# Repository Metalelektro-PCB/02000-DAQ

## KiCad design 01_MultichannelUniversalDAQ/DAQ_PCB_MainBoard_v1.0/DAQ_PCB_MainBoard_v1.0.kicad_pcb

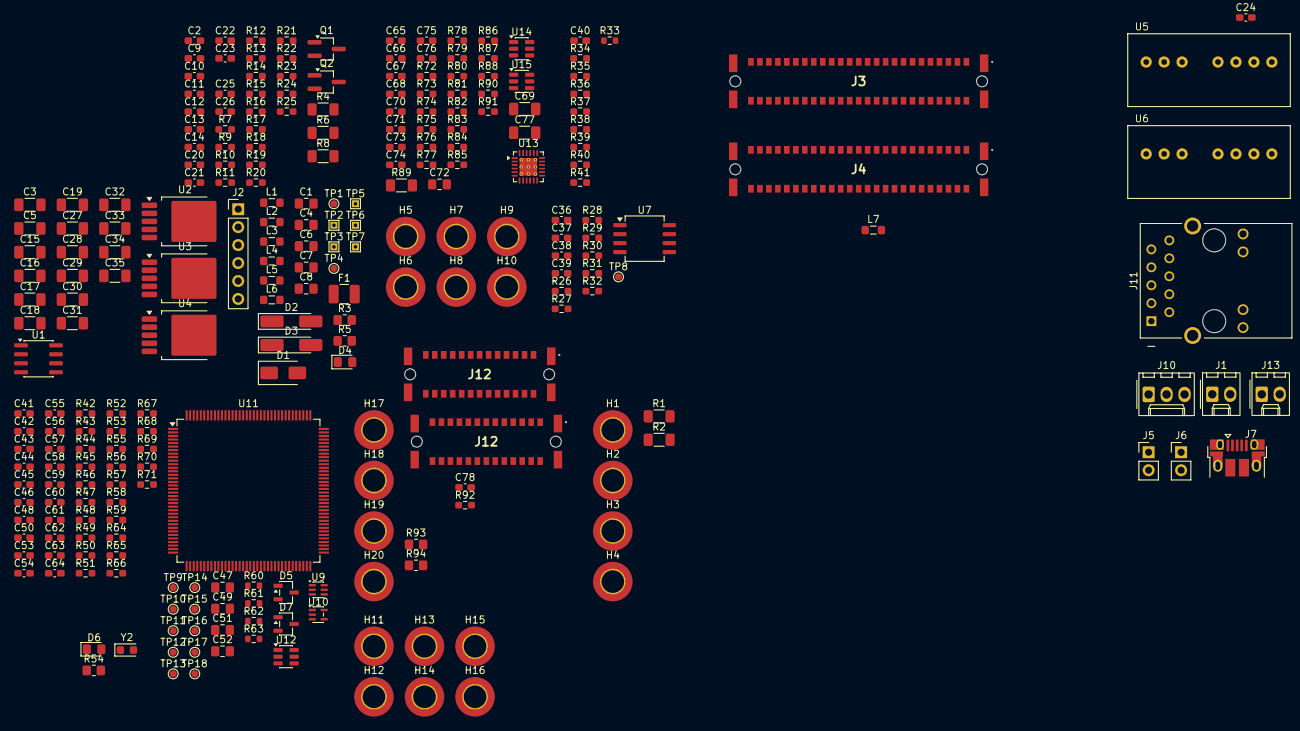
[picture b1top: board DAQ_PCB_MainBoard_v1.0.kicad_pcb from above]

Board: 2 copper layers, 254 parts (0 on the bottom side), 171 nets, no tracks yet.

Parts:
C1, C4, C6, C7, C8, C47, C49, C51, C52, C72: 2u2; C_0805_2012Metric_Pad1.18x1.45mm_HandSolder
C2, C60: 1u; C_0603_1608Metric_Pad1.08x0.95mm_HandSolder
C3, C5, C18, C19, C77: 470n; C_1206_3216Metric_Pad1.33x1.80mm_HandSolder
C9, C10, C11: 10n; C_0603_1608Metric_Pad1.08x0.95mm_HandSolder
C12, C13, C14, C24, C25, C26, C36, C37, C38, C39, C40, C41, C42, C43, C44, C45, C50, C53, C54, C55, C56, C57, C58, C59, C63, C64, C65, C68, C70, C71, C73, C75, C76, C78: 100n; C_0603_1608Metric_Pad1.08x0.95mm_HandSolder
C15, C16, C17, C27, C28, C29, C30, C31, C32, C33, C34, C35, C69: 10u; C_1206_3216Metric_Pad1.33x1.80mm_HandSolder
C20, C21, C22, C23, C74: 1n; C_0603_1608Metric_Pad1.08x0.95mm_HandSolder
C46, C48, C61, C62, C66, C67: 5p6; C_0603_1608Metric_Pad1.08x0.95mm_HandSolder
D1: SMAJ60CA; D_SMA
D2, D3: 10V; D_MiniMELF_Handsoldering
D4, D6: LED_RED; LED_0805_2012Metric_Pad1.15x1.40mm_HandSolder
D5, D7: 3V3; SOT-23-3
F1: Polyfuse_Small; Fuse_1210_3225Metric_Pad1.42x2.65mm_HandSolder
H1, H2, H3, H4, H5, H6, H7, H8, H9, H10, H11, H12, H13, H14, H15, H16, H17, H18, H19, H20: MountingHole_Pad; MountingHole_3.2mm_M3_DIN965_Pad_TopBottom
J1: Molex 1x2; Molex_KK-254_AE-6410-02A_1x02_P2.54mm_Vertical
J2: Pin Header 1x6; PinHeader_1x06_P2.54mm_Vertical
J3, J4: 15210502601000
J5, J6: 2.54 mm Header; PinHeader_1x02_P2.54mm_Vertical
J7: USB_B_Micro; USB_Micro-B_Amphenol_10103594-0001LF_Horizontal
J10: Molex 1x3; Molex_KK-254_AE-6410-03A_1x03_P2.54mm_Vertical
J11: 7499211121A; T_Wurth_WE-RJ45LAN_7499211121A
J12: Conn_02x13_Row_Letter_Last_MountingPin; 15210262601000
J12#2: 15210262601000
J13: Conn_01x02; Molex_KK-254_AE-6410-02A_1x02_P2.54mm_Vertical
L1, L2, L3, L4, L5, L6, L7: MPZ2012S601AT000; L_0805_2012Metric_Pad1.05x1.20mm_HandSolder
Q1, Q2: SQ2337CES; TSOT-23_HandSoldering
R1, R2, R4, R6, R8, R89: 0R; R_1206_3216Metric_Pad1.30x1.75mm_HandSolder
R3, R5: 100k; R_0805_2012Metric_Pad1.20x1.40mm_HandSolder
R7, R58, R59, R81: 1k5; R_0603_1608Metric_Pad0.98x0.95mm_HandSolder
R9, R12, R13, R14, R15, R16, R17, R18, R19, R20, R21, R22, R46, R47, R50, R51, R53, R64, R69, R70: 0R; R_0603_1608Metric_Pad0.98x0.95mm_HandSolder
R10, R11, R23, R24, R28, R29, R30, R35, R40, R44, R45, R77, R78, R79, R80, R82, R83: 10k; R_0603_1608Metric_Pad0.98x0.95mm_HandSolder
R25, R34, R36, R38, R42: 33k; R_0603_1608Metric_Pad0.98x0.95mm_HandSolder
R26, R27: 68k; R_0603_1608Metric_Pad0.98x0.95mm_HandSolder
R31: 1k; R_0603_1608Metric_Pad0.98x0.95mm_HandSolder
R32: 3k; R_0603_1608Metric_Pad0.98x0.95mm_HandSolder
R33, R60, R61, R62, R63: 0R; R_0603_1608Metric
R37: 47k; R_0603_1608Metric_Pad0.98x0.95mm_HandSolder
R39, R43: 12k; R_0603_1608Metric_Pad0.98x0.95mm_HandSolder
R41: 160k; R_0603_1608Metric_Pad0.98x0.95mm_HandSolder
R48, R49, R71, R90, R91: 470R; R_0603_1608Metric_Pad0.98x0.95mm_HandSolder
R52, R55, R56, R57, R65, R66, R67, R68, R72, R73, R74, R75, R76: 33R; R_0603_1608Metric_Pad0.98x0.95mm_HandSolder
R54, R94: 0R; R_0805_2012Metric_Pad1.20x1.40mm_HandSolder
R84, R86, R87, R88: 49R9; R_0603_1608Metric_Pad0.98x0.95mm_HandSolder
R85: 12k1; R_0603_1608Metric_Pad0.98x0.95mm_HandSolder
R92: 4k7; R_0603_1608Metric_Pad0.98x0.95mm_HandSolder
R93: 4k7; R_0805_2012Metric_Pad1.20x1.40mm_HandSolder
TP1, TP4, TP8, TP9, TP10, TP11, TP12, TP13, TP14, TP15, TP16, TP17, TP18: TestPoint; TestPoint_Pad_D1.0mm
TP2, TP3, TP5, TP6, TP7: TestPoint; TestPoint_THTPad_1.0x1.0mm_Drill0.5mm
U1: REF5050; SOIC-8_3.9x4.9mm_P1.27mm
U2, U3, U4: NCV8182C; TO-252-5_TabPin3
U5: DPBW06; SPBW03_DPBW03
U6: SPBW06; SPBW03_DPBW03
U7: INA823; SOIC-8_5.3x6.2mm_P1.27mm
U9: TPS22919; SOT-363_SC-70-6
U10: MCP9700Ax-ELT; SOT-353_SC-70-5
U11: STM32-H563ZI; LQFP-144_20x20mm_P0.5mm
U12, U14, U15: USBLC6-2SC6; SOT-23-6
U13: LAN8742AI; VQFN-24-1EP_4x4mm_P0.5mm_EP2.5x2.5mm_ThermalVias
Y2: 32.768kHz; Crystal_SMD_2012-2Pin_2.0x1.2mm_HandSoldering

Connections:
2V5: C12.1, C15.1, C41.1, J3.A8 (Pin_8a), J3.A9 (Pin_9a), J3.A10 (Pin_10a), J4.A8 (Pin_8a), J4.A9 (Pin_9a), J4.A10 (Pin_10a), R19.1, U2.2 (OUT), U9.1 (VIN)
3V3: C32.1, C35.1, C38.1, C40.1, C44.1, C51.1, C52.1, C53.1, C54.1, C55.1, C56.1, C57.1, C59.1, C65.1, C68.1, C78.1, J2.3, J3.A5 (Pin_5a), J3.A6 (Pin_6a), J3.A7 (Pin_7a), J4.A5 (Pin_5a), J4.A6 (Pin_6a), J4.A7 (Pin_7a), J5.2, J12#2.A10 (Pin_10a), J12#2.A11 (Pin_11a), L5.2, L7.1, R40.2, R42.2, R44.1, R46.2, R53.2, R54.2, R64.1, R71.1, R77.2, R78.2, R80.2, R81.2, R82.2, R83.2, R92.2, U7.7 (Vs+), U10.4 (V_{DD}), U11.17 (VDD), U11.30 (VDD), U11.39 (VDD), U11.52 (VDD), U11.62 (VDD), U11.72 (VDD), U11.84 (VDD), U11.95 (VDD), U11.106 (VDDUSB), U11.108 (VDD), U11.121 (VDDIO2), U11.131 (VDD), U11.144 (VDD), U13.9 (VDDIO)
5V: C13.1, C16.1, J2.4, J3.A12 (Pin_12a), J3.A13 (Pin_13a), J3.A14 (Pin_14a), J4.A12 (Pin_12a), J4.A13 (Pin_13a), J4.A14 (Pin_14a), J12#2.A5 (Pin_5a), J12#2.A6 (Pin_6a), R17.1, R18.1, R21.1, R36.2, U3.2 (OUT)
5Vref: C4.1, R7.2, R9.1, R12.1, R14.1, TP4.1 (1_1), U1.6 (Vout)
10V: C14.1, C17.1, J2.5, J3.A15 (Pin_15a), J3.A16 (Pin_16a), J3.A17 (Pin_17a), J4.A15 (Pin_15a), J4.A16 (Pin_16a), J4.A17 (Pin_17a), R23.1, U4.2 (OUT)
+12V: C1.1, C6.1, C7.1, C8.1, C30.1, C33.1, J2.6, J3.A19 (Pin_19a), J3.A20 (Pin_20a), J3.A21 (Pin_21a), J4.A19 (Pin_19a), J4.A20 (Pin_20a), J4.A21 (Pin_21a), L3.2, R25.2, R34.2, U1.2 (Vin), U2.1 (IN), U3.1 (IN), U4.1 (IN)
-12V: C31.2, C34.2, D4.1 (K), J2.1, J3.A22 (Pin_22a), J3.A23 (Pin_23a), J3.A24 (Pin_24a), J4.A22 (Pin_22a), J4.A23 (Pin_23a), J4.A24 (Pin_24a), L4.2, R33.1, R41.1
/DIGI_IO/EXTERNAL_TRIGGER: R92.1, U11.22 (PF10)
/DIGI_IO/ID.0: J12#2.B13 (Pin_13b), U11.114 (PD0)
/DIGI_IO/ID.1: J12#2.A7 (Pin_7a), U11.115 (PD1)
/DIGI_IO/ID.2: J12#2.A9 (Pin_9a), U11.116 (PD2)
/DIGI_IO/ID.3: J12#2.A12 (Pin_12a), U11.123 (PD7)
/DIGI_IO/SPI.CSn: J12#2.B6 (Pin_6b), U11.7 (PC13)
/DIGI_IO/SPI.MISO: J12#2.B3 (Pin_3b), TP11.1 (1_1), U11.112 (PC11)
/DIGI_IO/SPI.MOSI: J12#2.B4 (Pin_4b), TP12.1 (1_1), U11.113 (PC12)
/DIGI_IO/SPI.SCK: J12#2.B2 (Pin_2b), TP10.1 (1_1), U11.111 (PC10)
/DIGI_IO/TRIGGER_IN_GND: J13.2, R94.2
/DIGI_IO/TRIGGER_IN_SGN: J13.1, R93.1
/DIGI_IO/UART.CTS: J12#2.B8 (Pin_8b), U11.117 (PD3)
/DIGI_IO/UART.RTS: J12#2.B7 (Pin_7b), U11.118 (PD4)
/DIGI_IO/UART.RXD: J12#2.B10 (Pin_10b), U11.122 (PD6)
/DIGI_IO/UART.TXD: J12#2.B11 (Pin_11b), U11.119 (PD5)
/ETH/ETH_LED1: J11.11 (LED1_Y+), U13.3 (LED1/REGOFF)
/ETH/ETH_LED2: J11.13 (LED2_G+), U13.2 (LED2/~INTSEL)
/ETH/ETH_RBIAS: R85.1, U13.24 (RBIAS)
/ETH/ETH_RX_N: J11.2 (RD-), R84.2, U13.22 (RXN), U15.3 (I/O2), U15.4 (I/O2)
/ETH/ETH_RX_P: J11.1 (RD+), R86.2, U13.23 (RXP), U15.1 (I/O1), U15.6 (I/O1)
/ETH/ETH_TX_N: J11.6 (TD-), R87.2, U13.20 (TXN), U14.3 (I/O2), U14.4 (I/O2)
/ETH/ETH_TX_P: J11.5 (TD+), R88.2, U13.21 (TXP), U14.1 (I/O1), U14.6 (I/O1)
/ETH/RMII.CLK: R76.2, U11.35 (PA1)
/ETH/RMII.CRS: R74.2, U11.43 (PA7)
/ETH/RMII.MDC: U11.27 (PC1), U13.13 (MDC)
/ETH/RMII.MDIO: R81.1, U11.36 (PA2), U13.12 (MDIO)
/ETH/RMII.RSTn: R75.2, U11.26 (PC0)
/ETH/RMII.RXD0: R72.2, U11.44 (PC4)
/ETH/RMII.RXD1: R73.2, U11.45 (PC5)
/ETH/RMII.RXER: R79.2, U13.10 (RXER/PHYAD0)
/ETH/RMII.TXD0: R52.2, U13.17 (TXD0)
/ETH/RMII.TXD1: R57.1, U13.18 (TXD1)
/ETH/RMII.TXEN: U11.126 (PG11), U13.16 (TXEN)
/MCU/AUX_IO_0: D7.1 (K), J10.3, R58.1
/MCU/AUX_IO_1: D7.2 (K), J10.2, R59.1
/MCU/BOARD_TEMP: C45.1, R49.1, TP9.1 (1_1), U11.53 (PF13)
/MCU/DBG_VCC: C64.1, R71.2
/MCU/HW_CONFIG_0: R60.1, U11.79 (PD10)
/MCU/HW_CONFIG_1: R61.1, U11.80 (PD11)
/MCU/HW_CONFIG_2: R62.1, U11.81 (PD12)
/MCU/HW_CONFIG_3: R63.1, U11.82 (PD13)
/MCU/ID_1.0: J3.B20 (Pin_20b), U11.140 (PB9)
/MCU/ID_1.1: J3.B21 (Pin_21b), U11.69 (PB10)
/MCU/ID_1.2: J3.B22 (Pin_22b), U11.73 (PB12)
/MCU/ID_1.3: J3.B23 (Pin_23b), U11.74 (PB13)
/MCU/ID_2.0: J4.B20 (Pin_20b), U11.60 (PE9)
/MCU/ID_2.1: J4.B21 (Pin_21b), U11.63 (PE10)
/MCU/ID_2.2: J4.B22 (Pin_22b), U11.64 (PE11)
/MCU/ID_2.3: J4.B23 (Pin_23b), U11.90 (PG5)
/MCU/IO_1.0: J3.B7 (Pin_7b), U11.10 (PF0)
/MCU/IO_1.1: J3.B8 (Pin_8b), U11.11 (PF1)
/MCU/IO_1.2: J3.B10 (Pin_10b), U11.15 (PF5)
/MCU/IO_1.3: J3.B11 (Pin_11b), U11.12 (PF2)
/MCU/IO_1.4: J3.B12 (Pin_12b), U11.46 (PB0)
/MCU/IO_1.5: J3.B13 (Pin_13b), U11.47 (PB1)
/MCU/IO_1.6: J3.B15 (Pin_15b), U11.48 (PB2)
/MCU/IO_1.7: J3.B16 (Pin_16b), U11.96 (PC6)
/MCU/IO_1.8: J3.B17 (Pin_17b), U11.97 (PC7)
/MCU/IO_1.9: J3.B18 (Pin_18b), U11.98 (PC8)
/MCU/IO_2.0: J4.B7 (Pin_7b), U11.91 (PG6)
/MCU/IO_2.1: J4.B8 (Pin_8b), U11.92 (PG7)
/MCU/IO_2.2: J4.B10 (Pin_10b), U11.141 (PE0)
/MCU/IO_2.3: J4.B11 (Pin_11b), U11.1 (PE2)
/MCU/IO_2.4: J4.B12 (Pin_12b), U11.2 (PE3)
/MCU/IO_2.5: J4.B13 (Pin_13b), U11.3 (PE4)
/MCU/IO_2.6: J4.B15 (Pin_15b), U11.4 (PE5)
/MCU/IO_2.7: J4.B16 (Pin_16b), U11.5 (PE6)
/MCU/IO_2.8: J4.B17 (Pin_17b), U11.58 (PE7)
/MCU/IO_2.9: J4.B18 (Pin_18b), U11.59 (PE8)
/MCU/MCU_DBG_UART_RX: R65.2, U11.78 (PD9)
/MCU/MCU_DBG_UART_TX: R66.2, U11.77 (PD8)
/MCU/MCU_JTAG_TCK/SWCLK: R68.2, TP15.1 (1_1), U11.109 (PA14(JTCK)
/MCU/MCU_JTAG_TDI: TP16.1 (1_1), U11.110 (PA15(JTDI))
/MCU/MCU_JTAG_TDO: TP17.1 (1_1), U11.133 (PB3(JTDO)
/MCU/MCU_JTAG_TMS/SWDIO: R67.2, TP14.1 (1_1), U11.105 (PA13(JTMS)
/MCU/MCU_JTAG_TRSTn: TP18.1 (1_1), U11.134 (PB4(NJTRST))
/MCU/MCU_LED: R48.2, U11.14 (PF4)
/MCU/MCU_PROG: D5.1 (K), J5.1, R45.1, U11.138 (BOOT0)
/MCU/MCU_RSTn: C42.1, D5.2 (K), J6.2, R44.2, U11.25 (NRST)
/MCU/MCU_VREF: C43.1, R46.1, R47.2, U9.6 (VOUT), U11.32 (VREF+)
/MCU/PA0: TP13.1 (1_1), U11.34 (PA0)
/MCU/PWR_SENSE.BATT: C39.1, R31.1, R32.1, TP8.1 (1_1), U11.49 (PF11)
/MCU/SPI_1.CSn: J3.B6 (Pin_6b), U11.85 (PD14)
/MCU/SPI_1.MISO: J3.B2 (Pin_2b), U11.124 (PG9)
/MCU/SPI_1.MOSI: J3.B3 (Pin_3b), R56.1
/MCU/SPI_1.SCK: J3.B4 (Pin_4b), R55.1
/MCU/SPI_2.CSn: J4.B6 (Pin_6b), U11.68 (PE15)
/MCU/SPI_2.MISO: J4.B2 (Pin_2b), U11.66 (PE13)
/MCU/SPI_2.MOSI: J4.B3 (Pin_3b), U11.67 (PE14)
/MCU/SPI_2.SCK: J4.B4 (Pin_4b), U11.65 (PE12)
/MCU/USB_D_N: J7.2 (D-), U11.103 (PA11), U12.3 (I/O2), U12.4 (I/O2)
/MCU/USB_D_P: J7.3 (D+), U11.104 (PA12), U12.1 (I/O1), U12.6 (I/O1)
/PWR/VBAT_CON+: F1.1, J1.2
/PWR/VBAT_CON-: C3.2, C5.2, D1.1 (A1), J1.1, L2.1, R4.2, R5.1, R6.2, R8.2, R27.2
/PWR/VBAT_FUSE+: C3.1, D1.2 (A2), F1.2, Q2.3 (D)
/PWR/VIN+: C18.1, C19.1, C20.1, C22.1, L1.2, U5.2 (+VIN), U6.2 (+VIN)
/PWR/VIN-: C18.2, C19.2, C21.1, C23.1, L2.2, U5.1 (-VIN), U6.1 (-VIN)
/PWR/VIN_UNFILT+: C5.1, D2.1 (K), D3.1 (K), L1.1, Q1.2 (S), Q2.2 (S), R26.2, TP5.1 (1_1)
/VCC_PoE+: C77.1, J11.9 (V+), Q1.3 (D), TP2.1 (1_1)
/VCC_PoE-: C77.2, J11.10 (V-), R3.1, R8.1, TP3.1 (1_1)
GND: C1.2, C2.2, C4.2, C6.2, C7.2, C8.2, C9.2, C10.2, C11.2, C12.2, C13.2, C14.2, C15.2, C16.2, C17.2, C30.2, C31.1, C32.2, C33.2, C34.1, C35.2, C36.2, C37.1, C38.2, C39.2, C40.2, C41.2, C42.2, C43.2, C44.2, C45.2, C46.2, C47.2, C48.2, C49.2, C50.2, C51.2, C52.2, C53.2, C54.2, C55.2, C56.2, C57.2, C58.2, C59.2, C60.2, C61.2, C62.2, C63.2, C64.2, C65.2, C66.2, C67.2, C68.2, C69.2, C70.2, C71.2, C72.2, C73.2, C74.2, C75.2, C76.2, C78.2, D5.3 (A), D6.1 (K), D7.3 (A), J2.2, J3.51 (MountPin), J3.52 (MountPin), J3.53 (MountPin), J3.54 (MountPin), J3.A1 (Pin_1a), J3.A2 (Pin_2a), J3.A3 (Pin_3a), J3.A4 (Pin_4a), J3.A11 (Pin_11a), J3.A18 (Pin_18a), J3.A25 (Pin_25a), J3.B1 (Pin_1b), J3.B5 (Pin_5b), J3.B9 (Pin_9b), J3.B14 (Pin_14b), J3.B19 (Pin_19b), J3.B24 (Pin_24b), J3.B25 (Pin_25b), J4.51 (MountPin), J4.52 (MountPin), J4.53 (MountPin), J4.54 (MountPin), J4.A1 (Pin_1a), J4.A2 (Pin_2a), J4.A3 (Pin_3a), J4.A4 (Pin_4a), J4.A11 (Pin_11a), J4.A18 (Pin_18a), J4.A25 (Pin_25a), J4.B1 (Pin_1b), J4.B5 (Pin_5b), J4.B9 (Pin_9b), J4.B14 (Pin_14b), J4.B19 (Pin_19b), J4.B24 (Pin_24b), J4.B25 (Pin_25b), J6.1, J7.5 (GND), J7.6 (Shield), J10.1, J12#2.27 (MountPin), J12#2.28 (MountPin), J12#2.29 (MountPin), J12#2.30 (MountPin), J12#2.A1 (Pin_1a), J12#2.A2 (Pin_2a), J12#2.A3 (Pin_3a), J12#2.A4 (Pin_4a), J12#2.A8 (Pin_8a), J12#2.A13 (Pin_13a), J12#2.B1 (Pin_1b), J12#2.B5 (Pin_5b), J12#2.B9 (Pin_9b), J12#2.B12 (Pin_12b), L6.2, R1.2, R2.2, R6.1, R7.1, R11.2, R13.2, R16.2, R20.2, R22.2, R24.2, R28.2, R29.1, R32.2, R35.1, R37.1, R39.1, R43.1, R45.2, R50.1, R51.1, R60.2, R61.2, R62.2, R63.2, R70.1, R79.1, R85.2, R90.1, R91.1, R94.1, TP6.1 (1_1), TP7.1 (1_1), U1.4 (GND), U2.3 (GND), U3.3 (GND), U4.3 (GND), U7.4 (Vs-), U7.5 (Ref), U9.2 (GND), U10.2 (GND), U11.16 (VSS), U11.31 (VSSA), U11.38 (VSS), U11.51 (VSS), U11.61 (VSS), U11.71 (VSS), U11.83 (VSS), U11.94 (VSS), U11.107 (VSS), U11.120 (VSS), U11.130 (VSS), U11.143 (VSS), U12.2 (GND), U13.25 (VSS), U14.2 (GND), U15.2 (GND)
MGND: H1.1 (1_1), R1.1, R2.1, R4.1, R89.1
unnamed: C47.1, U11.70 (VCAP)
unnamed: C49.1, U11.142 (VCAP)
unnamed: D2.2 (A), Q1.1 (G), R3.2
unnamed: D3.2 (A), Q2.1 (G), R5.2
unnamed: D4.2 (A), R25.1
unnamed: D6.2 (A), R48.1
unnamed: J7.4 (ID), R70.2
unnamed: J7.1 (VBUS), R69.1
unnamed: J11.12 (LED1_Y-), R91.2
unnamed: J11.14 (LED2_G-), R90.2
unnamed: J11.S1 (SHIELD1), J11.S2 (SHIELD2), R89.2
unnamed: R9.2, R10.1, R17.2
unnamed: R14.2, R15.1, R18.2
unnamed: R30.1, U7.1 (Rg)
unnamed: R30.2, U7.8 (Rg)
unnamed: R31.2, U7.6
unnamed: TP1.1 (1_1), U1.3 (Temp)
unnamed: C2.1, U1.5 (Trim/NR)
unnamed: R19.2, R20.1, U2.4 (ADJ)
unnamed: C9.1, R10.2, R11.1, U2.5 (V_{REF/EN})
unnamed: R21.2, R22.1, U3.4 (ADJ)
unnamed: C10.1, R12.2, R13.1, U3.5 (V_{REF/EN})
unnamed: R23.2, R24.1, U4.4 (ADJ)
unnamed: C11.1, R15.2, R16.1, U4.5 (V_{REF/EN})
unnamed: C20.2, C24.1, C27.1, L3.1, U5.6 (+VOUT)
unnamed: C21.2, C25.2, C28.2, L4.1, U5.8 (-VOUT)
unnamed: C24.2, C25.1, C27.2, C28.1, U5.7 (COM)
unnamed: C22.2, C26.1, C29.1, L5.1, U6.6 (+VOUT)
unnamed: C23.2, C26.2, C29.2, L6.1, U6.7 (-VOUT)
unnamed: C36.1, R26.1, R28.1, U7.3 (+)
unnamed: C37.2, R27.1, R29.2, U7.2 (-)
unnamed: R34.1, R35.2
unnamed: R36.1, R37.2
unnamed: R38.1, R39.2
unnamed: R40.1, R41.2
unnamed: R42.1, R43.2, U9.3 (ON)
unnamed: R47.1, U9.5 (QOD)
unnamed: R49.2, U10.3 (V_{OUT})
unnamed: R55.2, U11.41 (PA5)
unnamed: R56.2, U11.135 (PB5)
unnamed: R58.2, U11.136 (PB6)
unnamed: R59.2, U11.137 (PB7)
unnamed: R57.2, U11.76 (PB15)
unnamed: C61.1, U11.8 (PC14), Y2.2
unnamed: C62.1, U11.9 (PC15), Y2.1
unnamed: R50.2, U11.50 (PF12)
unnamed: R51.2, U11.54 (PF14)
unnamed: R52.1, U11.128 (PG13)
unnamed: C46.1, U11.23 (PH0)
unnamed: C48.1, U11.24 (PH1)
unnamed: C50.1, R53.1, U11.6 (VBAT)
unnamed: C58.1, C60.1, R54.1, U11.33 (VDDA)
unnamed: C63.1, R64.2, R69.2, U12.5 (VBUS)
unnamed: R74.1, R80.1, U13.11 (CRS_DV/MODE2)
unnamed: R72.1, R77.1, U13.8 (RXD0/MODE0)
unnamed: R73.1, R78.1, U13.7 (RXD1/MODE1)
unnamed: C66.1, U13.5 (XTAL1/CLKIN)
unnamed: C67.1, U13.4 (XTAL2)
unnamed: R76.1, R83.1, U13.14 (~INT/REFCLKO)
unnamed: R75.1, R82.1, U13.15 (~RST)
VA: C69.1, C70.1, C71.1, C75.1, C76.1, J11.3 (CRD), J11.4 (CTD), L7.2, R84.1, R86.1, R87.1, R88.1, U13.1 (VDD2A), U13.19 (VDD1A), U14.5 (VBUS), U15.5 (VBUS)
VCR: C72.1, C73.1, C74.1, U13.6 (VDDCR)

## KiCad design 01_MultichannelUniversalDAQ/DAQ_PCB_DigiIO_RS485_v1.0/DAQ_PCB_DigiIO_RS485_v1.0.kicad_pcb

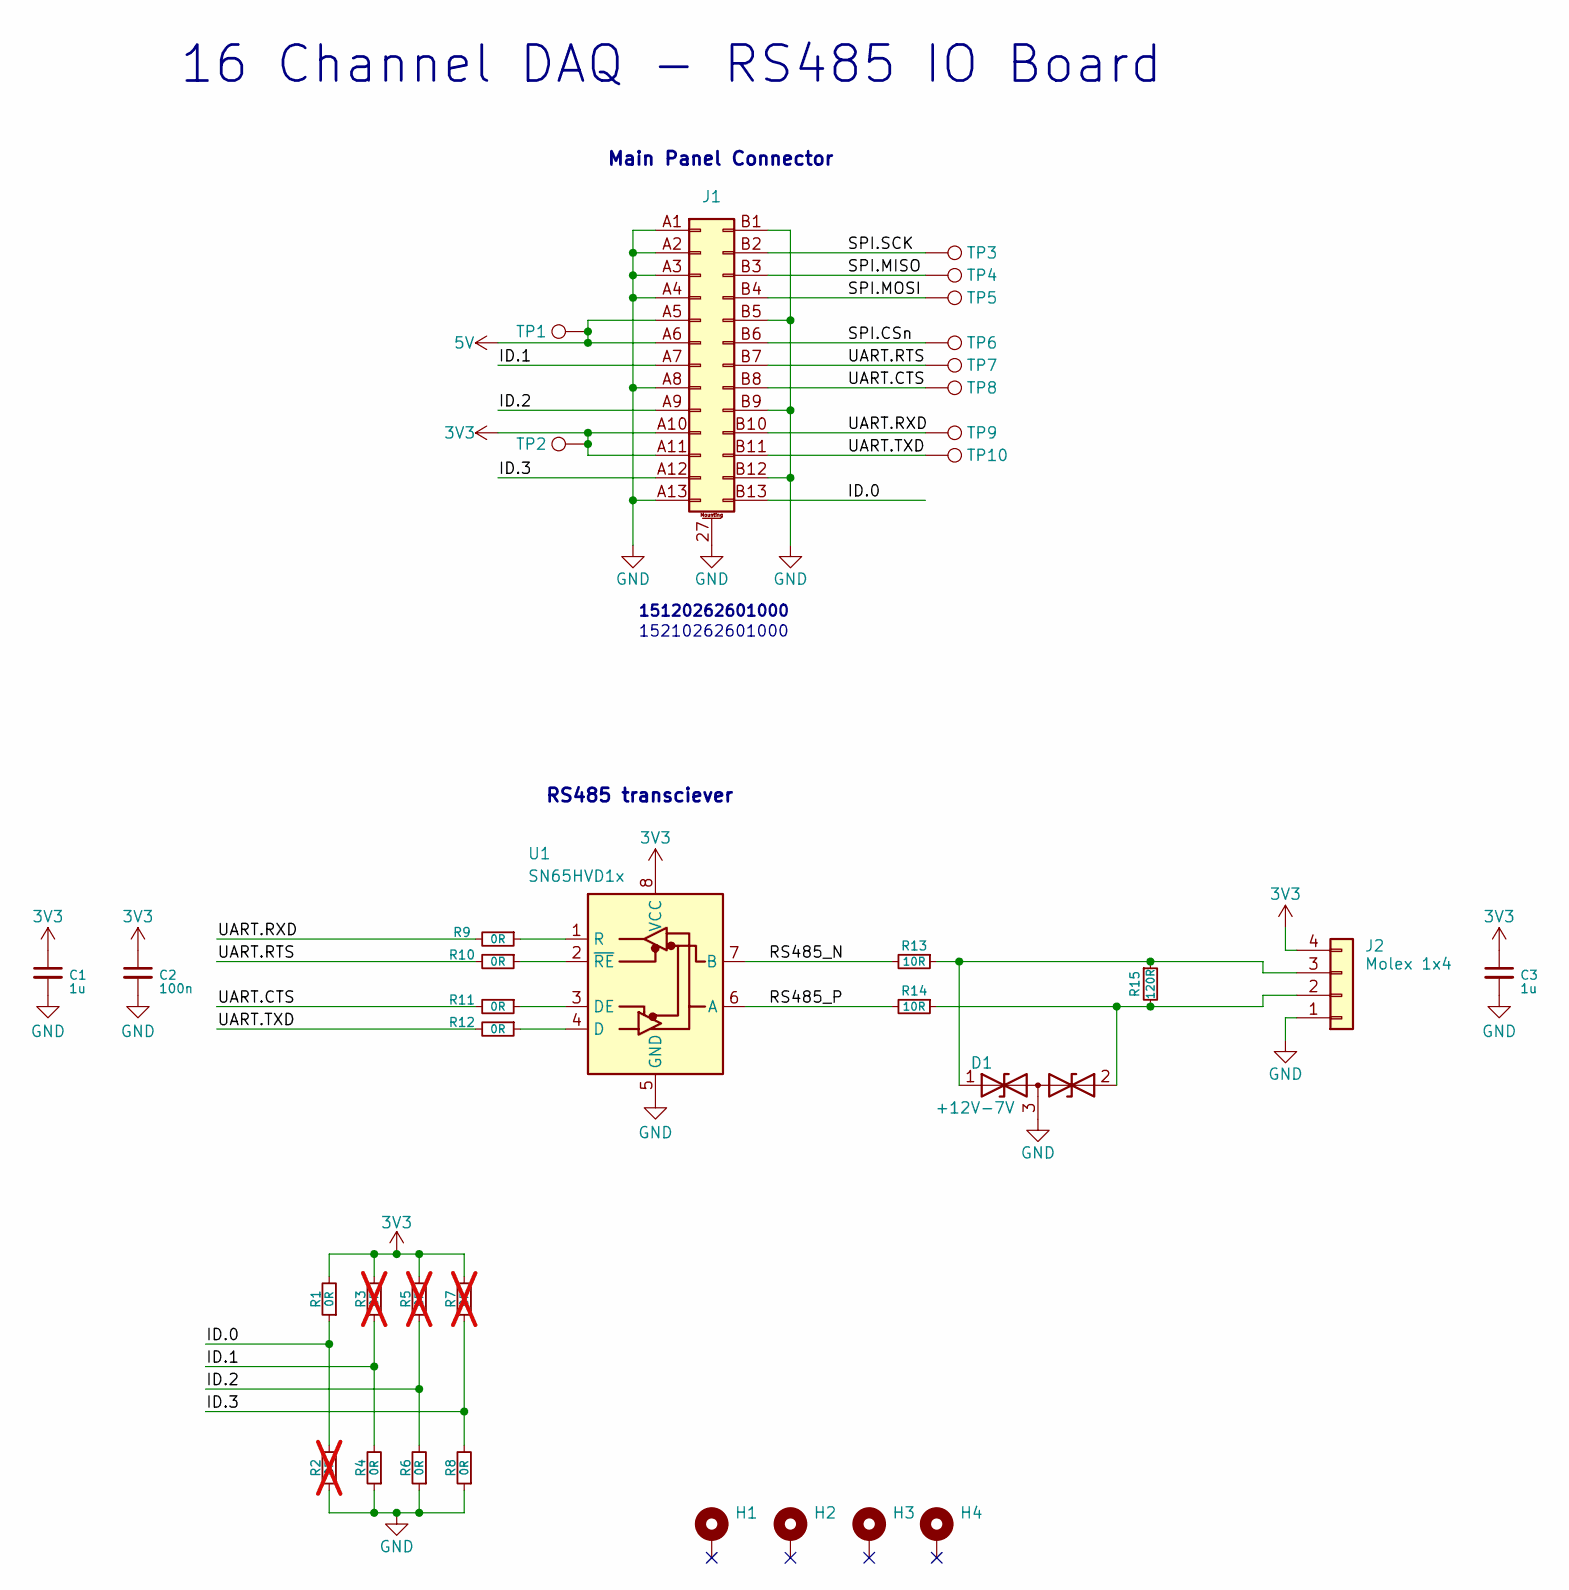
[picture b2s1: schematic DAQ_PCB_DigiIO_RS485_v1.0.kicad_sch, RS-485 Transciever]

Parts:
C1, C3: 1u; C_0603_1608Metric_Pad1.08x0.95mm_HandSolder
C2: 100n; C_0603_1608Metric_Pad1.08x0.95mm_HandSolder
D1: +12V-7V; SOT-323_SC-70; Part Number PEC33712C2A_R1_00001
H1, H2, H3, H4: MountingHole_Pad; MountingHole_3.2mm_M3_DIN965_Pad_TopBottom
J1: 15120262601000; Part Number 15120262601000
J2: Molex 1x4; Molex_KK-254_AE-6410-04A_1x04_P2.54mm_Vertical
R1, R4, R6, R8: 0R; R_0603_1608Metric_Pad0.98x0.95mm_HandSolder
R2, R3, R5, R7: 0R; R_0603_1608Metric_Pad0.98x0.95mm_HandSolder; not fitted
R9, R10, R11, R12: 0R; R_0805_2012Metric_Pad1.20x1.40mm_HandSolder
R13, R14: 10R; R_0805_2012Metric_Pad1.20x1.40mm_HandSolder
R15: 120R; R_1206_3216Metric_Pad1.30x1.75mm_HandSolder
TP1, TP2, TP3, TP4, TP5, TP6, TP7, TP8, TP9, TP10: TestPoint; TestPoint_Pad_D1.0mm
U1: SN65HVD1x; SOIC-8_3.9x4.9mm_P1.27mm; Part Number SN65HVD11DR

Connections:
3V3: C1.1, C2.1, C3.1, J1.A10 (Pin_10a), J1.A11 (Pin_11a), J2.4, R1.2, R3.2, R5.2, R7.2, TP2.1 (1_1), U1.8 (VCC)
5V: J1.A5 (Pin_5a), J1.A6 (Pin_6a), TP1.1 (1_1)
/ID.0: J1.B13 (Pin_13b), R1.1, R2.2
/ID.1: J1.A7 (Pin_7a), R3.1, R4.2
/ID.2: J1.A9 (Pin_9a), R5.1, R6.2
/ID.3: J1.A12 (Pin_12a), R7.1, R8.2
/RS485_N: R13.2, U1.7 (B)
/RS485_P: R14.2, U1.6 (A)
/SPI.CSn: J1.B6 (Pin_6b), TP6.1 (1_1)
/SPI.MISO: J1.B3 (Pin_3b), TP4.1 (1_1)
/SPI.MOSI: J1.B4 (Pin_4b), TP5.1 (1_1)
/SPI.SCK: J1.B2 (Pin_2b), TP3.1 (1_1)
/UART.CTS: J1.B8 (Pin_8b), R11.2, TP8.1 (1_1)
/UART.RTS: J1.B7 (Pin_7b), R10.2, TP7.1 (1_1)
/UART.RXD: J1.B10 (Pin_10b), R9.2, TP9.1 (1_1)
/UART.TXD: J1.B11 (Pin_11b), R12.2, TP10.1 (1_1)
GND: C1.2, C2.2, C3.2, D1.3 (common), J1.27 (MountPin), J1.28 (MountPin), J1.29 (MountPin), J1.30 (MountPin), J1.A1 (Pin_1a), J1.A2 (Pin_2a), J1.A3 (Pin_3a), J1.A4 (Pin_4a), J1.A8 (Pin_8a), J1.A13 (Pin_13a), J1.B1 (Pin_1b), J1.B5 (Pin_5b), J1.B9 (Pin_9b), J1.B12 (Pin_12b), J2.1, R2.1, R4.1, R6.1, R8.1, U1.5 (GND)
unnamed: D1.1 (A1), J2.3, R13.1, R15.1
unnamed: D1.2 (A2), J2.2, R14.1, R15.2
unnamed: R12.1, U1.4 (D)
unnamed: R11.1, U1.3 (DE)
unnamed: R9.1, U1.1 (R)
unnamed: R10.1, U1.2 (~RE)

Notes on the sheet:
Main Panel Connector
16 Channel DAQ - RS485 IO Board
RS485 transciever
15210262601000
15120262601000

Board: 2 copper layers, 36 parts (1 on the bottom side), 23 nets, no tracks yet.

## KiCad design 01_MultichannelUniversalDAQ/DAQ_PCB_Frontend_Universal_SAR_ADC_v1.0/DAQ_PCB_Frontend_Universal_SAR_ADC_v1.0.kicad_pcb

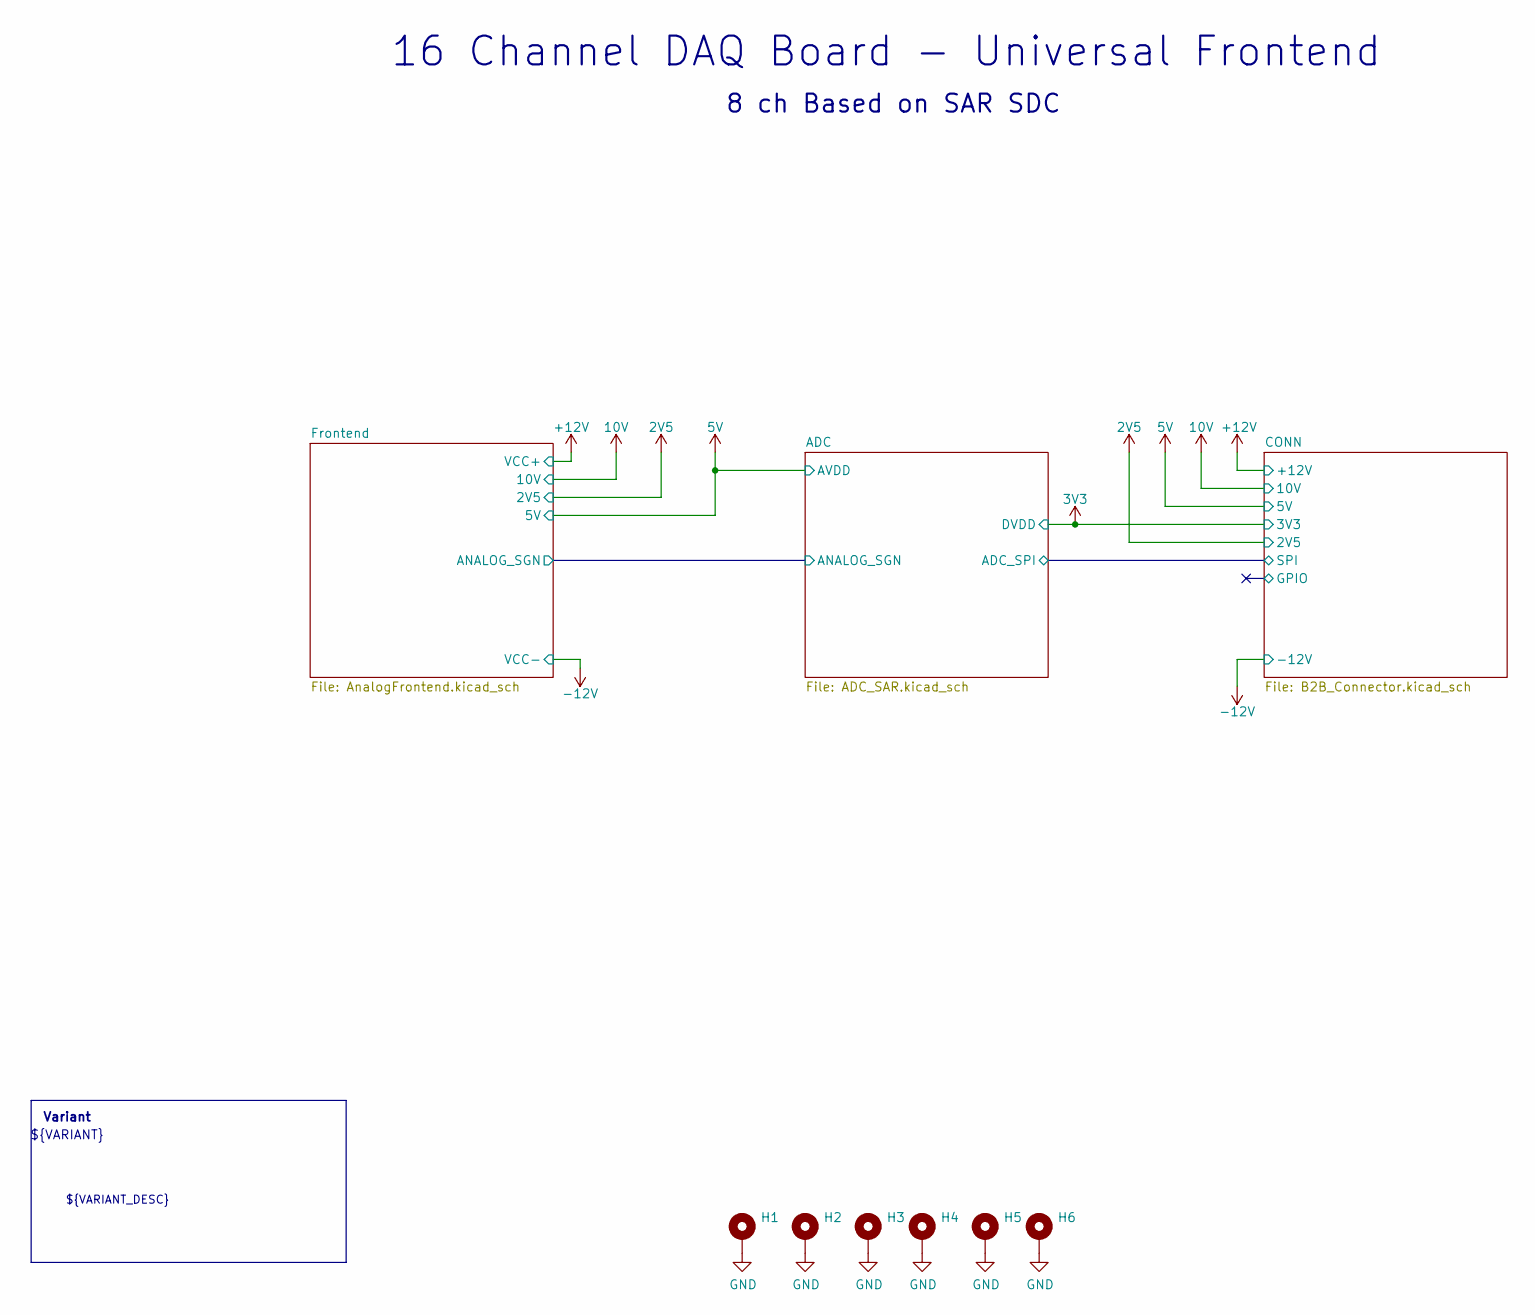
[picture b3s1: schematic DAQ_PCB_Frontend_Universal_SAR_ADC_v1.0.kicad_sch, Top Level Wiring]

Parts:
H1, H2, H3, H4, H5, H6: MountingHole_Pad; MountingHole_3.2mm_M3_DIN965_Pad_TopBottom

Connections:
GND: H1.1 (1_1), H2.1 (1_1), H3.1 (1_1), H4.1 (1_1), H5.1 (1_1), H6.1 (1_1); also elsewhere on the board

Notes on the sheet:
${VARIANT}
16 Channel DAQ Board - Universal Frontend
Variant
8 ch Based on SAR SDC
${VARIANT_DESC}

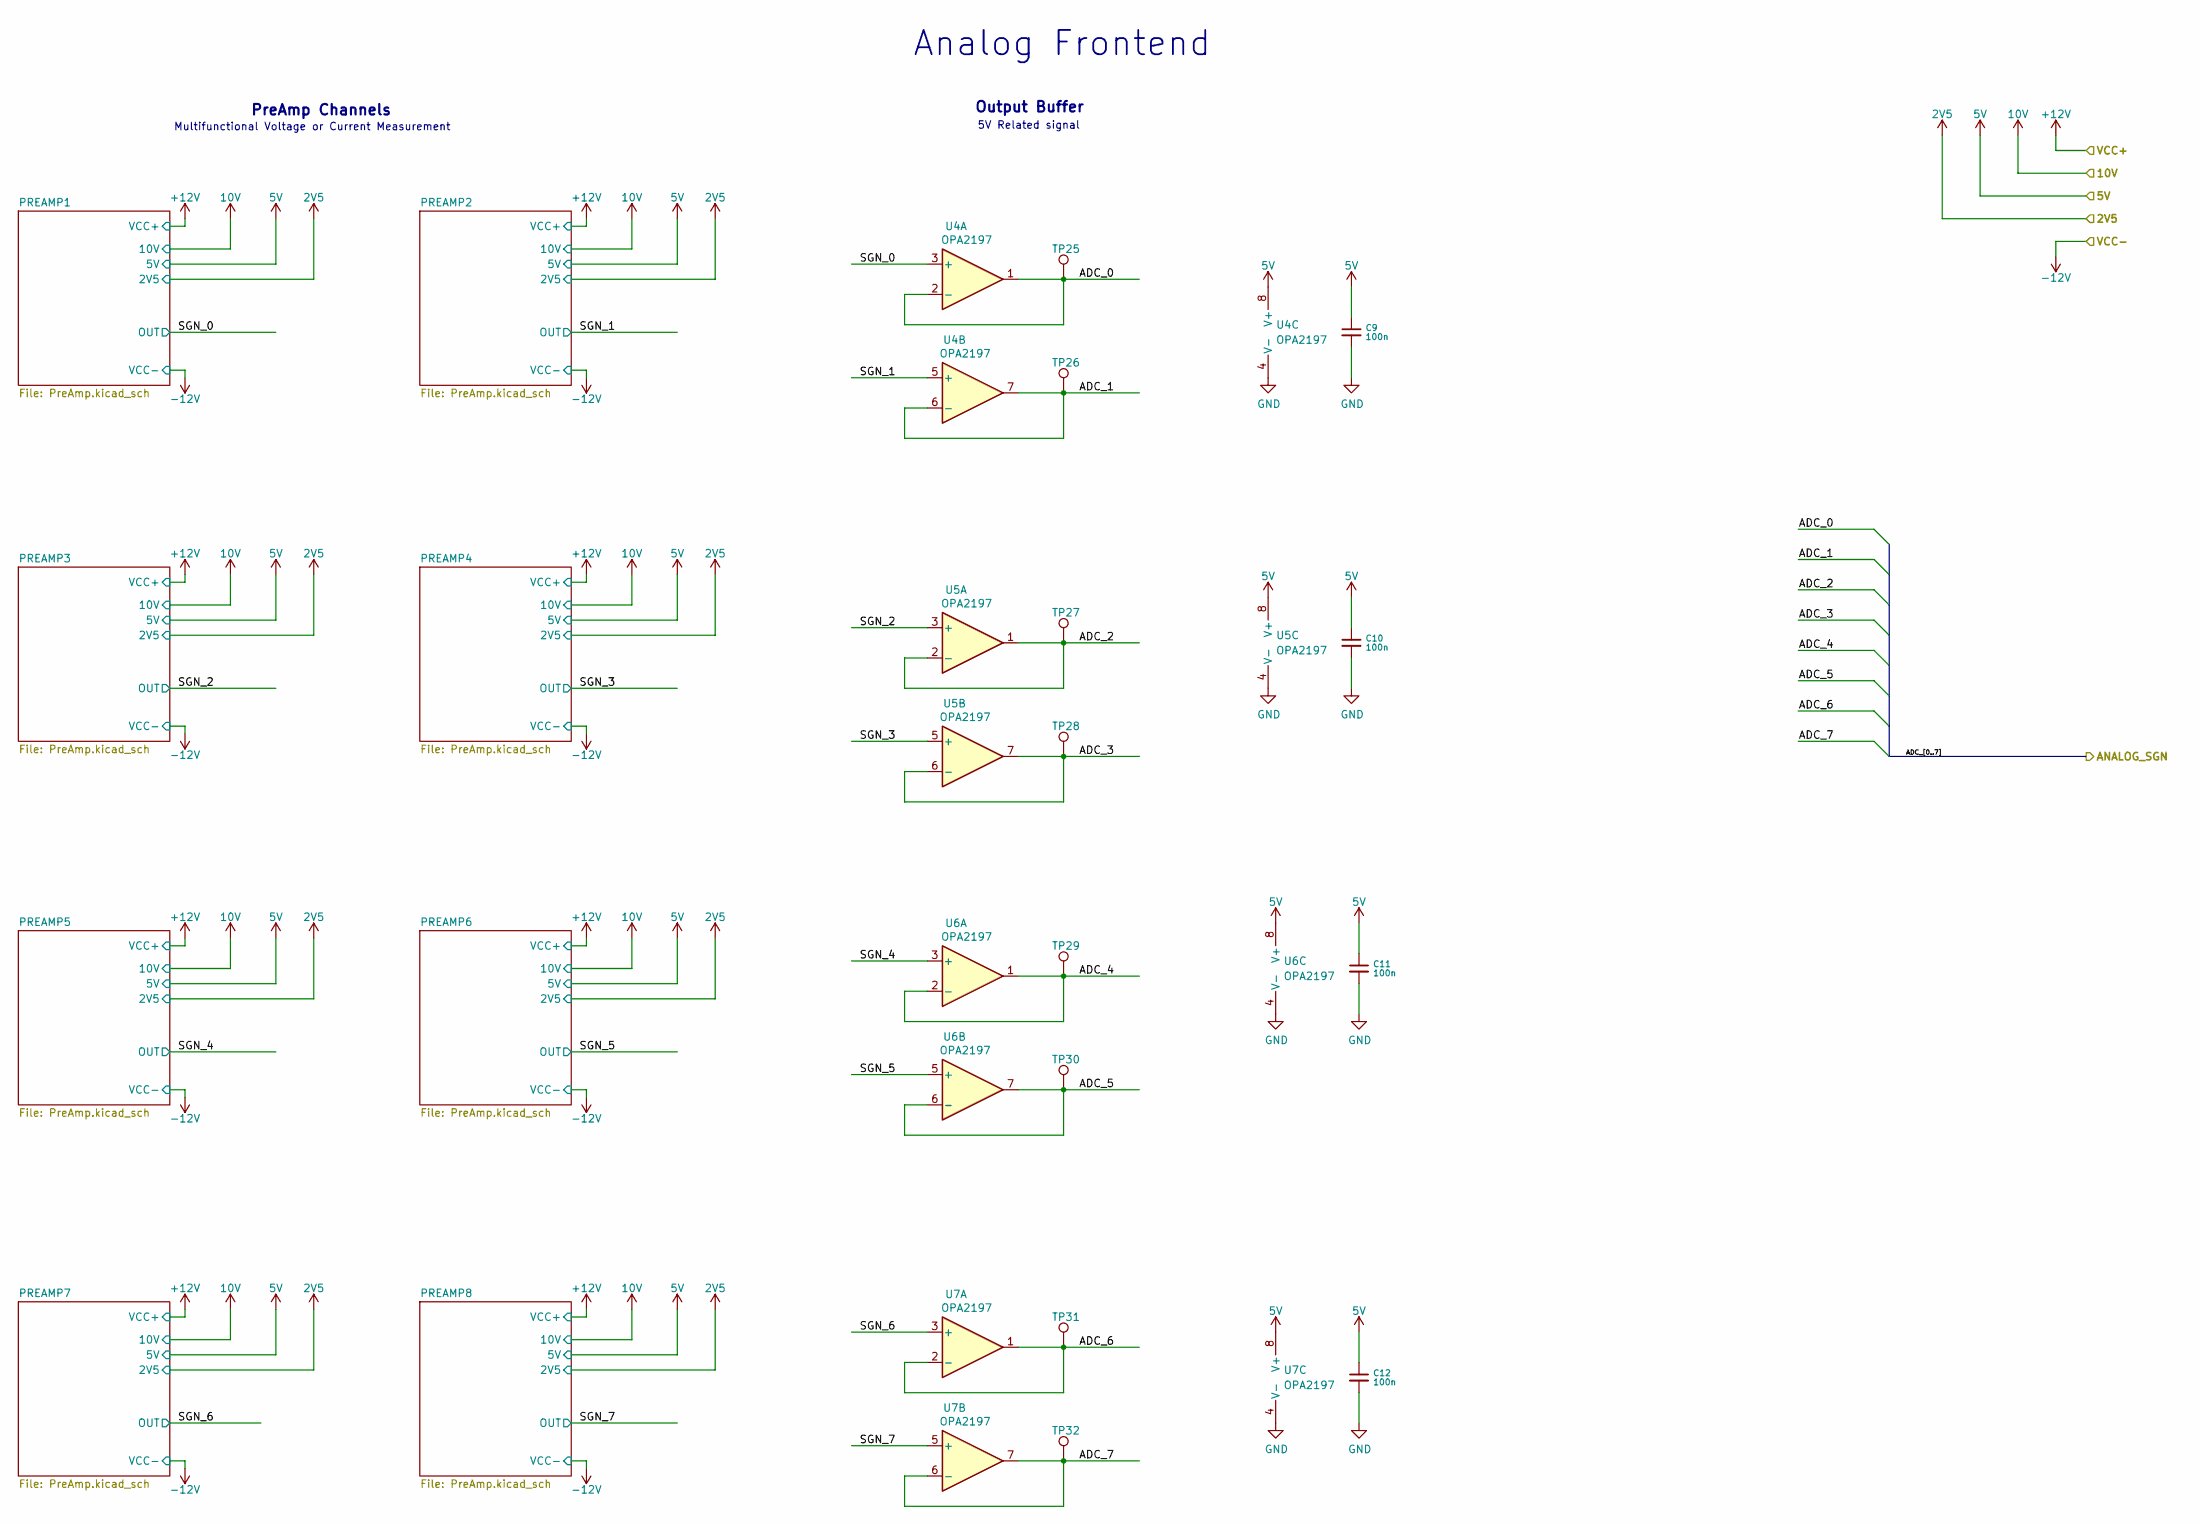
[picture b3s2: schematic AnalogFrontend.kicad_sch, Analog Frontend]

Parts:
C9, C10, C11, C12: 100n; C_0603_1608Metric_Pad1.08x0.95mm_HandSolder
TP25, TP26, TP27, TP28, TP29, TP30, TP31, TP32: TestPoint; TestPoint_Pad_D1.0mm
U4, U5, U6, U7: OPA2197; SOIC-8_3.9x4.9mm_P1.27mm; Part Number OPA2197IDR

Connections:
5V: C9.1, C10.1, C11.1, C12.1, U4.8 (V+), U5.8 (V+), U6.8 (V+), U7.8 (V+); also elsewhere on the board
/ADC/ADC_0: TP25.1 (1_1), U4.1, U4.2 (-); also elsewhere on the board
/ADC/ADC_1: TP26.1 (1_1), U4.6 (-), U4.7; also elsewhere on the board
/ADC/ADC_2: TP27.1 (1_1), U5.1, U5.2 (-); also elsewhere on the board
/ADC/ADC_3: TP28.1 (1_1), U5.6 (-), U5.7; also elsewhere on the board
/ADC/ADC_4: TP29.1 (1_1), U6.1, U6.2 (-); also elsewhere on the board
/ADC/ADC_5: TP30.1 (1_1), U6.6 (-), U6.7; also elsewhere on the board
/ADC/ADC_6: TP31.1 (1_1), U7.1, U7.2 (-); also elsewhere on the board
/ADC/ADC_7: TP32.1 (1_1), U7.6 (-), U7.7; also elsewhere on the board
/Frontend/SGN_0: U4.3 (+); also elsewhere on the board
/Frontend/SGN_1: U4.5 (+); also elsewhere on the board
/Frontend/SGN_2: U5.3 (+); also elsewhere on the board
/Frontend/SGN_3: U5.5 (+); also elsewhere on the board
/Frontend/SGN_4: U6.3 (+); also elsewhere on the board
/Frontend/SGN_5: U6.5 (+); also elsewhere on the board
/Frontend/SGN_6: U7.3 (+); also elsewhere on the board
/Frontend/SGN_7: U7.5 (+); also elsewhere on the board
GND: C9.2, C10.2, C11.2, C12.2, U4.4 (V-), U5.4 (V-), U6.4 (V-), U7.4 (V-); also elsewhere on the board

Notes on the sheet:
Analog Frontend
5V Related signal
Multifunctional Voltage or Current Measurement
PreAmp Channels
Output Buffer

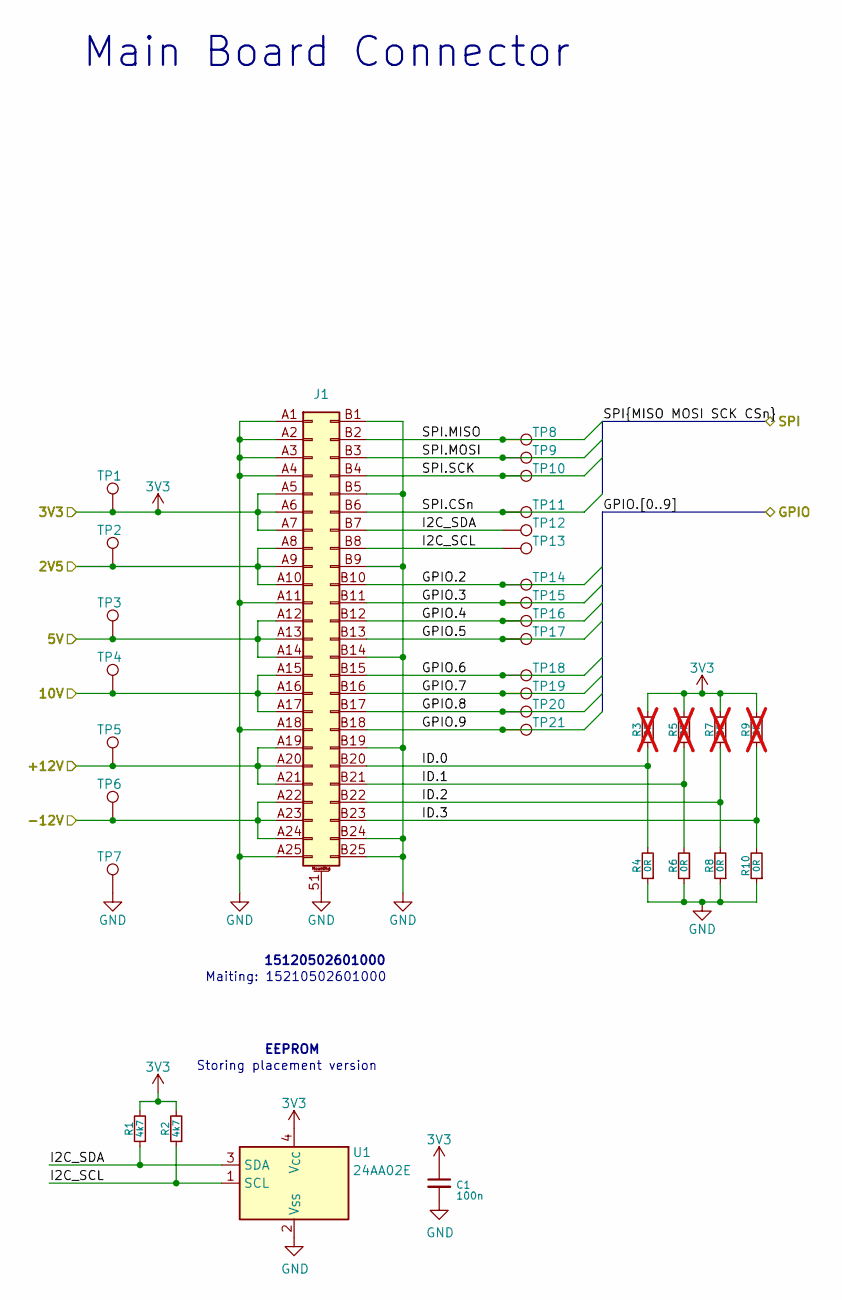
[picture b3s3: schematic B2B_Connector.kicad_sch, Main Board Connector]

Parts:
C1: 100n; C_0603_1608Metric_Pad1.08x0.95mm_HandSolder
J1: 15120502601000; Part Number 15120502601000
R1, R2: 4k7; R_0603_1608Metric_Pad0.98x0.95mm_HandSolder
R3, R5, R7, R9: 0R; R_0603_1608Metric_Pad0.98x0.95mm_HandSolder; not fitted
R4, R6, R8, R10: 0R; R_0603_1608Metric_Pad0.98x0.95mm_HandSolder
TP1, TP2, TP3, TP4, TP5, TP6, TP7, TP8, TP9, TP10, TP11, TP12, TP13, TP14, TP15, TP16, TP17, TP18, TP19, TP20, TP21: TestPoint; TestPoint_Pad_D1.0mm
U1: 24AA02E; SOT-23-5; Part Number 24AA02E48T-I/OT

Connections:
2V5: J1.A8 (Pin_8a), J1.A9 (Pin_9a), J1.A10 (Pin_10a), TP2.1 (1_1); also elsewhere on the board
3V3: C1.1, J1.A5 (Pin_5a), J1.A6 (Pin_6a), J1.A7 (Pin_7a), R1.2, R2.2, R3.2, R5.2, R7.2, R9.2, TP1.1 (1_1), U1.4 (V_{CC}); also elsewhere on the board
5V: J1.A12 (Pin_12a), J1.A13 (Pin_13a), J1.A14 (Pin_14a), TP3.1 (1_1); also elsewhere on the board
10V: J1.A15 (Pin_15a), J1.A16 (Pin_16a), J1.A17 (Pin_17a), TP4.1 (1_1); also elsewhere on the board
+12V: J1.A19 (Pin_19a), J1.A20 (Pin_20a), J1.A21 (Pin_21a), TP5.1 (1_1); also elsewhere on the board
-12V: J1.A22 (Pin_22a), J1.A23 (Pin_23a), J1.A24 (Pin_24a), TP6.1 (1_1); also elsewhere on the board
/ADC/ADC_SPI.CSn: J1.B6 (Pin_6b), TP11.1 (1_1); also elsewhere on the board
/ADC/ADC_SPI.MISO: J1.B2 (Pin_2b), TP8.1 (1_1); also elsewhere on the board
/ADC/ADC_SPI.MOSI: J1.B3 (Pin_3b), TP9.1 (1_1); also elsewhere on the board
/ADC/ADC_SPI.SCK: J1.B4 (Pin_4b), TP10.1 (1_1); also elsewhere on the board
/CONN/GPIO.2: J1.B10 (Pin_10b), TP14.1 (1_1)
/CONN/GPIO.3: J1.B11 (Pin_11b), TP15.1 (1_1)
/CONN/GPIO.4: J1.B12 (Pin_12b), TP16.1 (1_1)
/CONN/GPIO.5: J1.B13 (Pin_13b), TP17.1 (1_1)
/CONN/GPIO.6: J1.B15 (Pin_15b), TP18.1 (1_1)
/CONN/GPIO.7: J1.B16 (Pin_16b), TP19.1 (1_1)
/CONN/GPIO.8: J1.B17 (Pin_17b), TP20.1 (1_1)
/CONN/GPIO.9: J1.B18 (Pin_18b), TP21.1 (1_1)
/CONN/I2C_SCL: J1.B8 (Pin_8b), R2.1, TP13.1 (1_1), U1.1 (SCL)
/CONN/I2C_SDA: J1.B7 (Pin_7b), R1.1, TP12.1 (1_1), U1.3 (SDA)
/CONN/ID.0: J1.B20 (Pin_20b), R3.1, R4.2
/CONN/ID.1: J1.B21 (Pin_21b), R5.1, R6.2
/CONN/ID.2: J1.B22 (Pin_22b), R7.1, R8.2
/CONN/ID.3: J1.B23 (Pin_23b), R9.1, R10.2
GND: C1.2, J1.51 (MountPin), J1.52 (MountPin), J1.53 (MountPin), J1.54 (MountPin), J1.A1 (Pin_1a), J1.A2 (Pin_2a), J1.A3 (Pin_3a), J1.A4 (Pin_4a), J1.A11 (Pin_11a), J1.A18 (Pin_18a), J1.A25 (Pin_25a), J1.B1 (Pin_1b), J1.B5 (Pin_5b), J1.B9 (Pin_9b), J1.B14 (Pin_14b), J1.B19 (Pin_19b), J1.B24 (Pin_24b), J1.B25 (Pin_25b), R4.1, R6.1, R8.1, R10.1, TP7.1 (1_1), U1.2 (V_{SS}); also elsewhere on the board

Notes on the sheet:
Storing placement version
Main Board Connector
Maiting: 15210502601000
15120502601000
EEPROM
